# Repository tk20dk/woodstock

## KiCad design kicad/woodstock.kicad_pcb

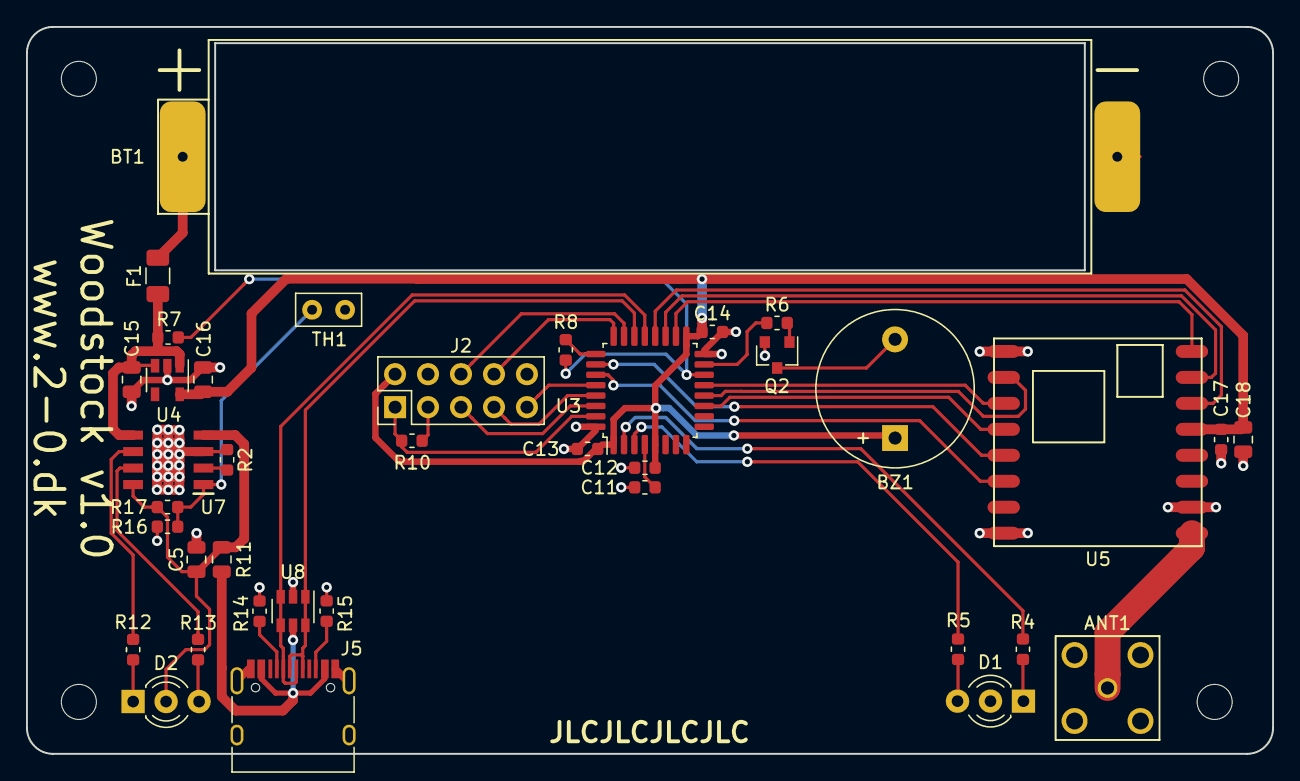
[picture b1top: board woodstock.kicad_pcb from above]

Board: 2 copper layers, 96.0 x 56.0 mm, 42 parts (0 on the bottom side), 41 nets.

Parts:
ANT1: SMA; CON-SMA
BT1: 3.7v; 18650
BZ1: Buzzer; Buzzer_12x9.5RM7.6
C5, C15, C16, C18: 10u; C_0805_2012Metric
C11, C12, C13, C14, C17: 100n; C_0603_1608Metric
D1: red/green; LED_D3.0mm-3
D2: chrg/stby; LED_D3.0mm-3
F1: 1A; Fuse_1206_3216Metric
H1, H2, H3, H4: MountingHole; MountingHole_2.7mm
J2: Debug; PinHeader_2x05_P2.54mm_Vertical
J5: USB-C; USB_C_Receptacle_HRO_TYPE-C-31-M-12
Q2: AO3400A; SOT-23
R2: 1.2k; R_0603_1608Metric
R4, R5, R6: 470; R_0603_1608Metric
R7: 75k; R_0603_1608Metric
R8: 150k; R_0603_1608Metric
R10: 100k; R_0603_1608Metric
R11: 0.4; R_0805_2012Metric
R12, R13: 1k; R_0603_1608Metric
R14, R15: 5.1k; R_0603_1608Metric
R16, R17: R; R_0603_1608Metric
TH1: 10k; NTC_th
U3: STM32L062K8Tx; LQFP-32_7x7mm_P0.8mm
U4: TPS7A2-3.0; SOT-23-5
U5: RFM96W-433; RFM95W
U7: TP4056; SOIC127P600X175-9N
U8: SRV05-4; SOT-23-6

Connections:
+3V3: BZ1.1, C12.1, C13.1, C14.1, C16.1, C17.1, C18.1, J2.2, U3.1, U3.5, U3.17, U4.5, U5.13
GND: ANT1.2, BT1.2, C5.2, C11.2, C12.2, C13.2, C14.2, C15.2, C16.2, C17.2, C18.2, D1.2, J2.3, J2.4, J2.10, J5.A1, J5.A12, J5.B1, J5.B12, J5.S1, Q2.2, R2.2, R10.1, R14.1, R15.1, R16.2, TH1.1, U3.16, U3.32, U4.2, U5.1, U5.8, U5.10, U7.3, U7.9, U8.2
unnamed: ANT1.1, U5.9
unnamed: BT1.1, F1.2
unnamed: BZ1.2, Q2.3
unnamed: C5.1, D2.2, R11.1, R17.2, U7.4, U7.8
unnamed: C15.1, F1.1, R7.1, U4.1, U4.3, U7.5
unnamed: D1.1, R4.2
unnamed: D1.3, R5.1
unnamed: D2.1, R12.1
unnamed: D2.3, R13.2
unnamed: J5.A5, R14.2
unnamed: J5.B5, R15.2
unnamed: Q2.1, R6.1
unnamed: R2.1, U7.2
unnamed: R12.2, U7.6
unnamed: R13.1, U7.7
unnamed: R16.1, R17.1, TH1.2, U7.1
adc_vbat: R7.2, R8.1, U3.14
boot0: J2.1, R10.2, U3.31
hmi_buzzer: R6.2, U3.15
hmi_green: R5.2, U3.3
hmi_red: R4.1, U3.2
nrst: C11.1, U3.4
pb5: J2.9, U3.28
pwr_sensor: R8.2, U3.25
radio_cs: U3.26, U5.5
radio_dio0: U3.20, U5.14
radio_dio1: U3.19, U5.15
radio_dio2: U3.18, U5.16
radio_reset: U3.27, U5.6
spi_miso: U3.12, U5.2
spi_mosi: U3.13, U5.3
spi_sck: U3.11, U5.4
swclk: J2.8, U3.24
swdio: J2.6, U3.23
uart_rx: J2.5, U3.30
uart_tx: J2.7, U3.29
usb_dm: J5.A7, J5.B7, U3.21, U8.3, U8.4
usb_dp: J5.A6, J5.B6, U3.22, U8.1, U8.6
vusb: J5.A4, J5.A9, J5.B4, J5.B9, R11.2, U8.5

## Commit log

2020-11-20 created initial kicad project
